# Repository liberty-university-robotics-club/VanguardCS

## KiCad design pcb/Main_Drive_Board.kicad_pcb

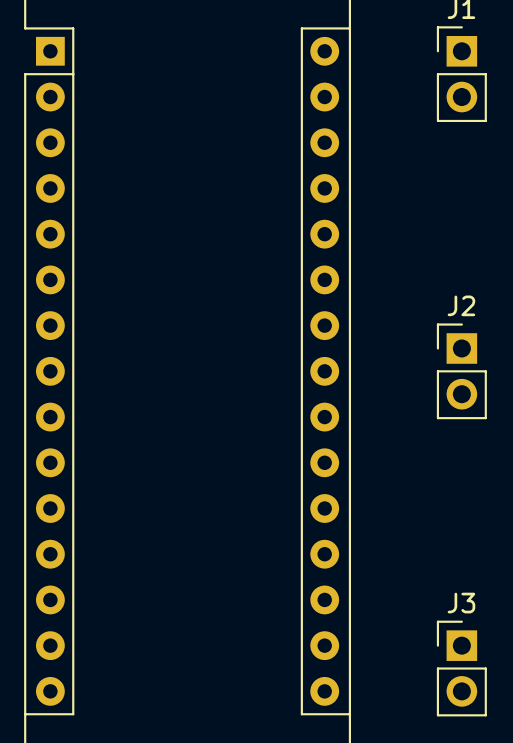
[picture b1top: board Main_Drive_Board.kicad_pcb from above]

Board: 2 copper layers, 4 parts (0 on the bottom side), 2 nets, no tracks yet.

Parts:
A1: Arduino_Nano_v3.x; Arduino_Nano
J1, J2, J3: Conn_01x02_Male; PinHeader_1x02_P2.54mm_Vertical

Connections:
unnamed: A1.23, J1.1, J2.1, J3.1
unnamed: A1.24, J1.2, J2.2, J3.2

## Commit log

2019-01-30 added test code for drive motor control
2019-02-07 add better functionality to drive motor control
2019-02-13 nightly
2019-02-13 Create LICENSE
2019-02-13 started new version of motor control
2019-02-19 started adding framework for spi communication
2019-02-20 added more code for spi framework
2019-02-22 added pinMode to attempt to make it work
2019-02-23 started transition to i2c because of pin conflicts with spi
2019-03-05 i think i2c is working now
2019-04-30 added motor control pcb schematics
2019-05-28 serial test code
2019-06-19 added class to handle serial communication
2019-08-22 attempted to add serial read ability
2019-08-27 current
2019-08-27 test
2019-09-29 Added ROS install script for debian
2019-10-01 fixed error in instal script
2019-10-09 updated install script
2019-11-23 added ROS workspace
2019-11-23 testing
2019-12-05 removed catkin workspace
2019-12-07 drive turtle around with udp
2019-12-07 decent trade off between quality bandwidth and latency
2019-12-07 forgot this
2020-01-03 fixes
2020-01-28 updated to ros2
2020-01-28 updated file name
